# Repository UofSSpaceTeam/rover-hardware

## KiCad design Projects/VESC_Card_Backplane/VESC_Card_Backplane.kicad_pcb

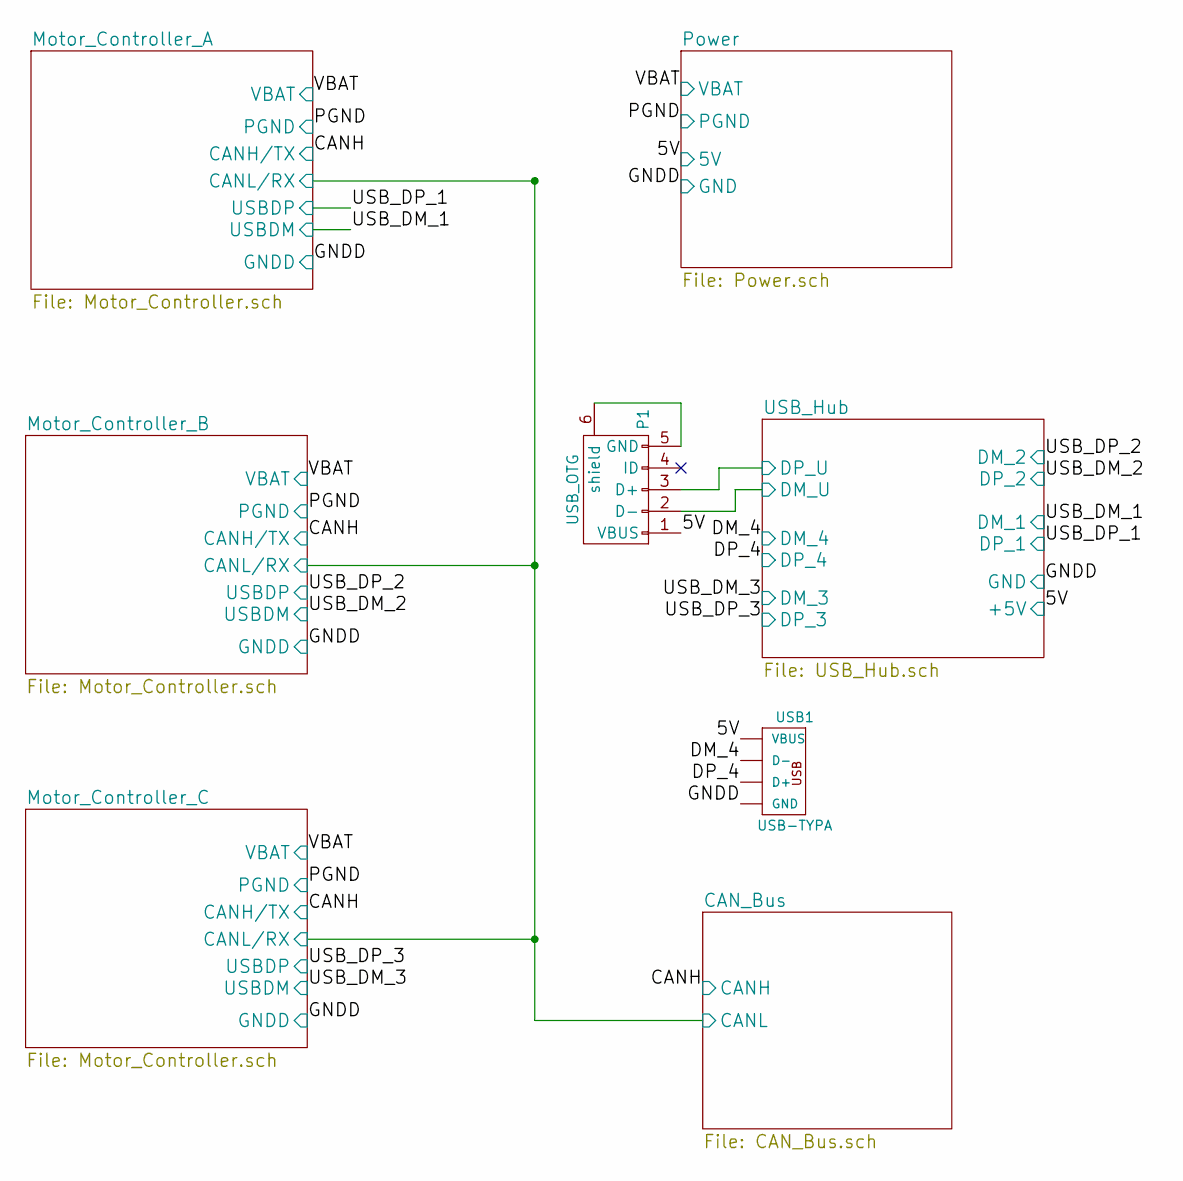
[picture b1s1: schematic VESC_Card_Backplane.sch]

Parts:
P1: USB_OTG; USB_Mini-B
USB1: USB-TYPA; USB_A_PTH_AMP787616-1

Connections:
/DM_4: USB1.D-; also elsewhere on the board
/DP_4: USB1.D+; also elsewhere on the board
/USB_Hub/DM_U: P1.2 (D-); also elsewhere on the board
/USB_Hub/DP_U: P1.3 (D+); also elsewhere on the board

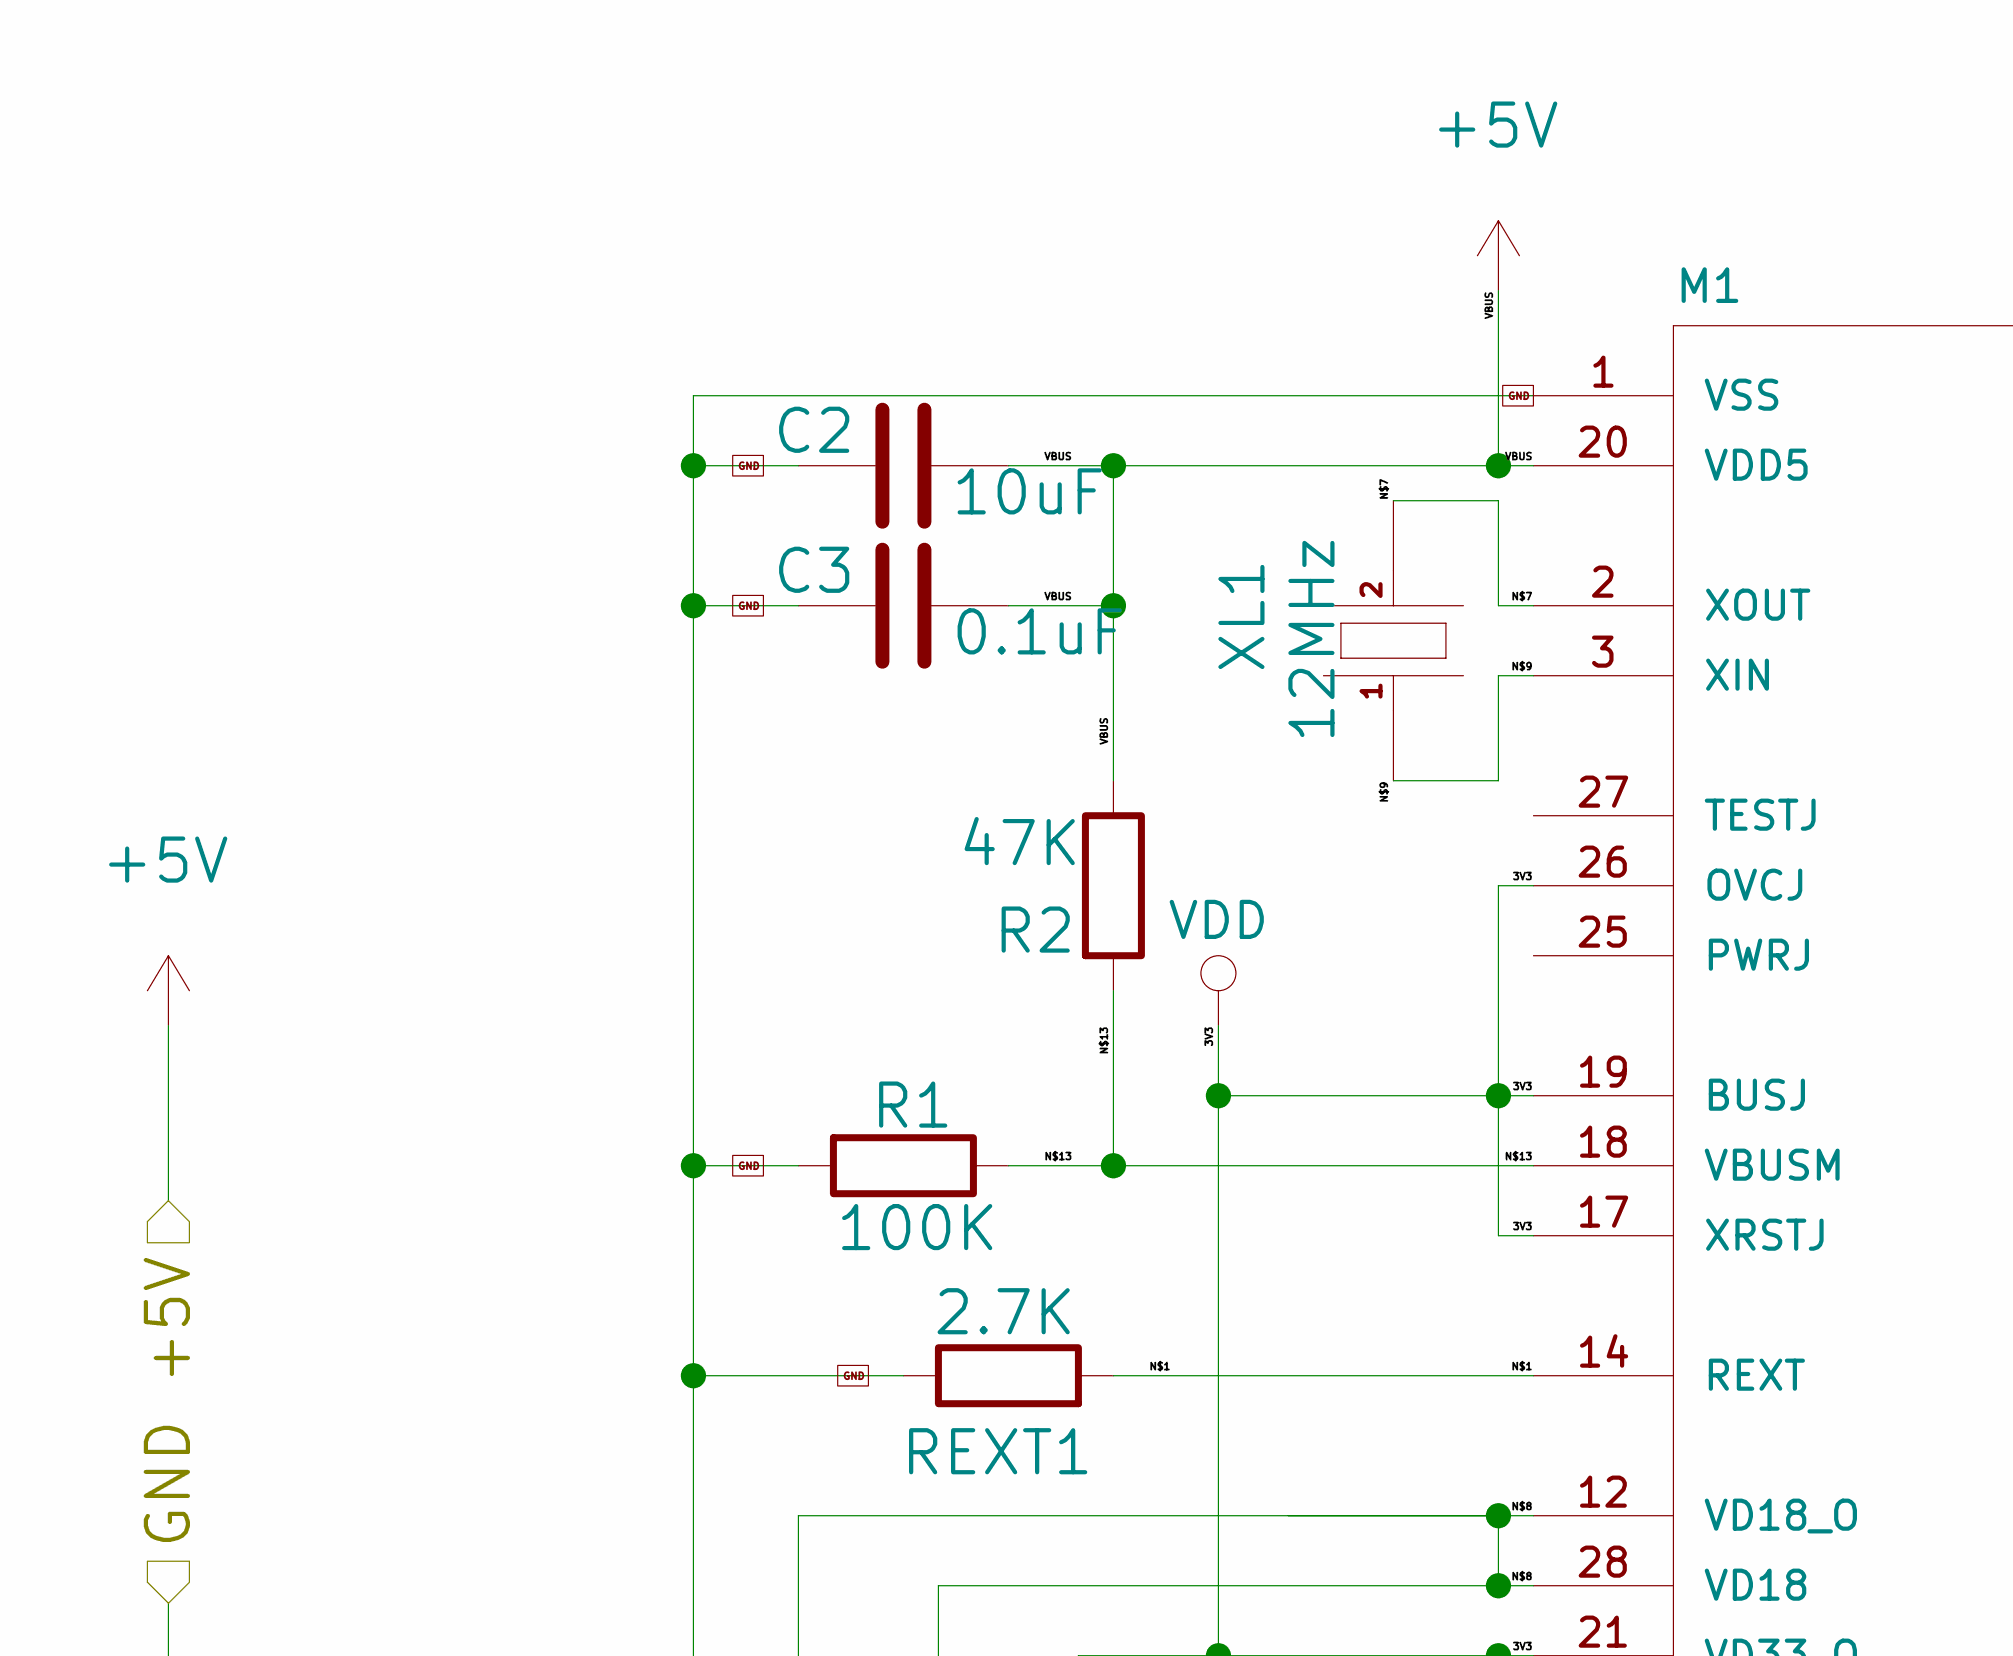
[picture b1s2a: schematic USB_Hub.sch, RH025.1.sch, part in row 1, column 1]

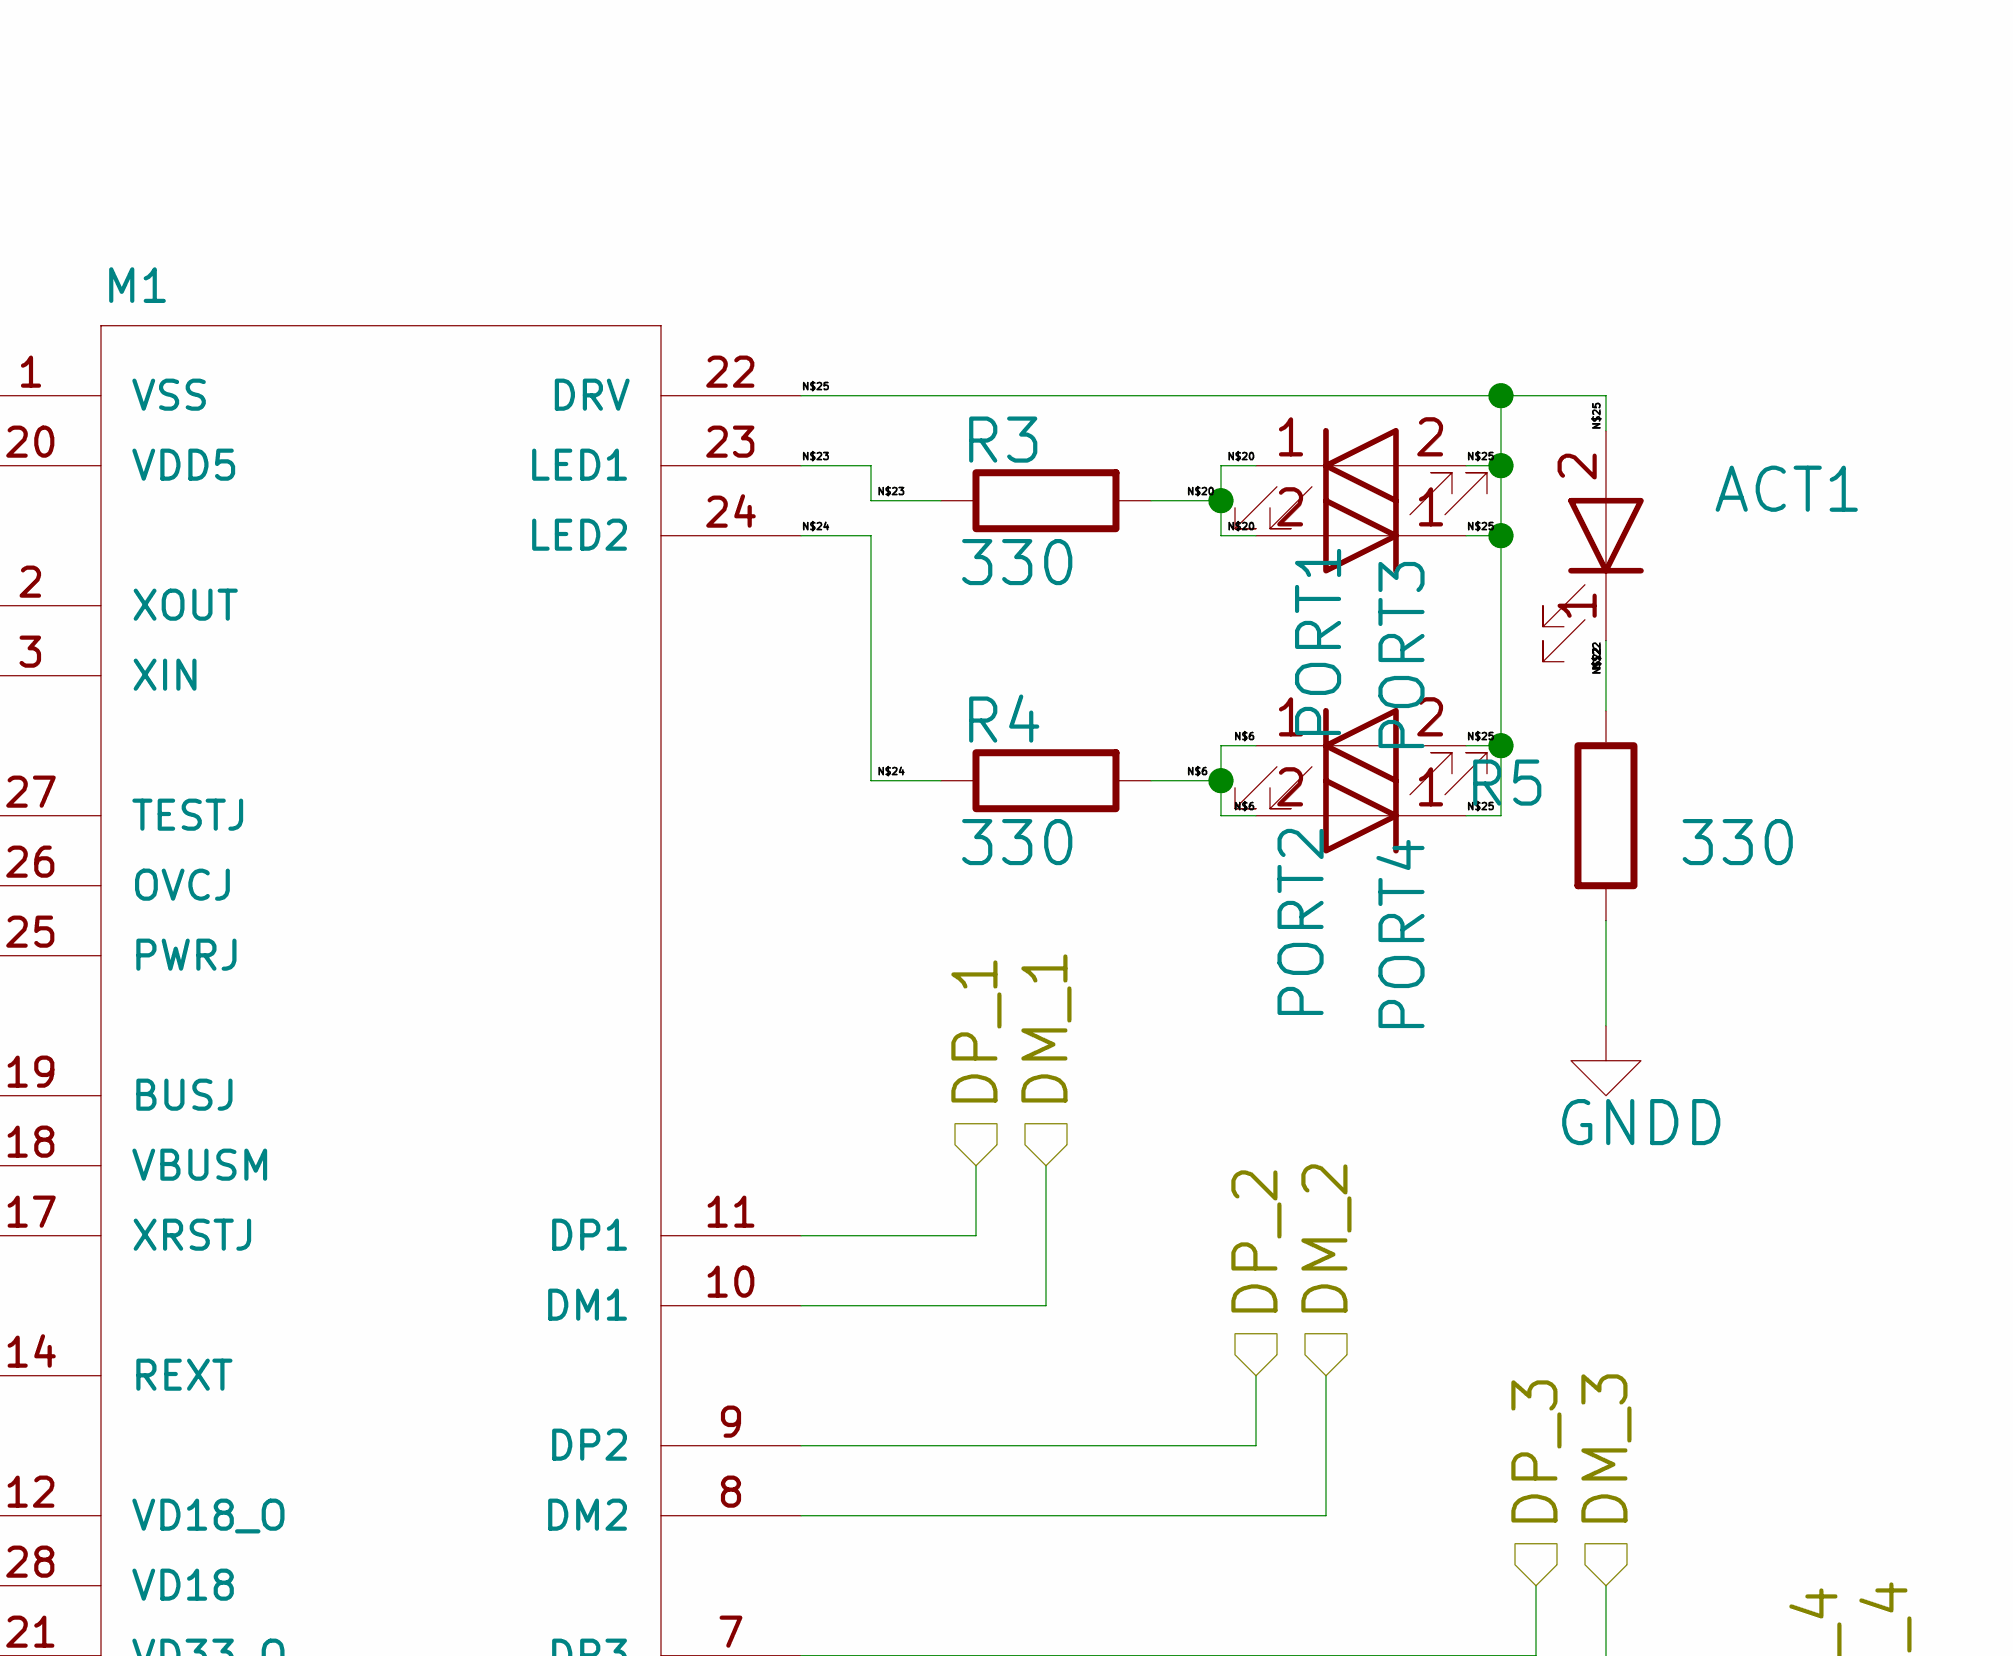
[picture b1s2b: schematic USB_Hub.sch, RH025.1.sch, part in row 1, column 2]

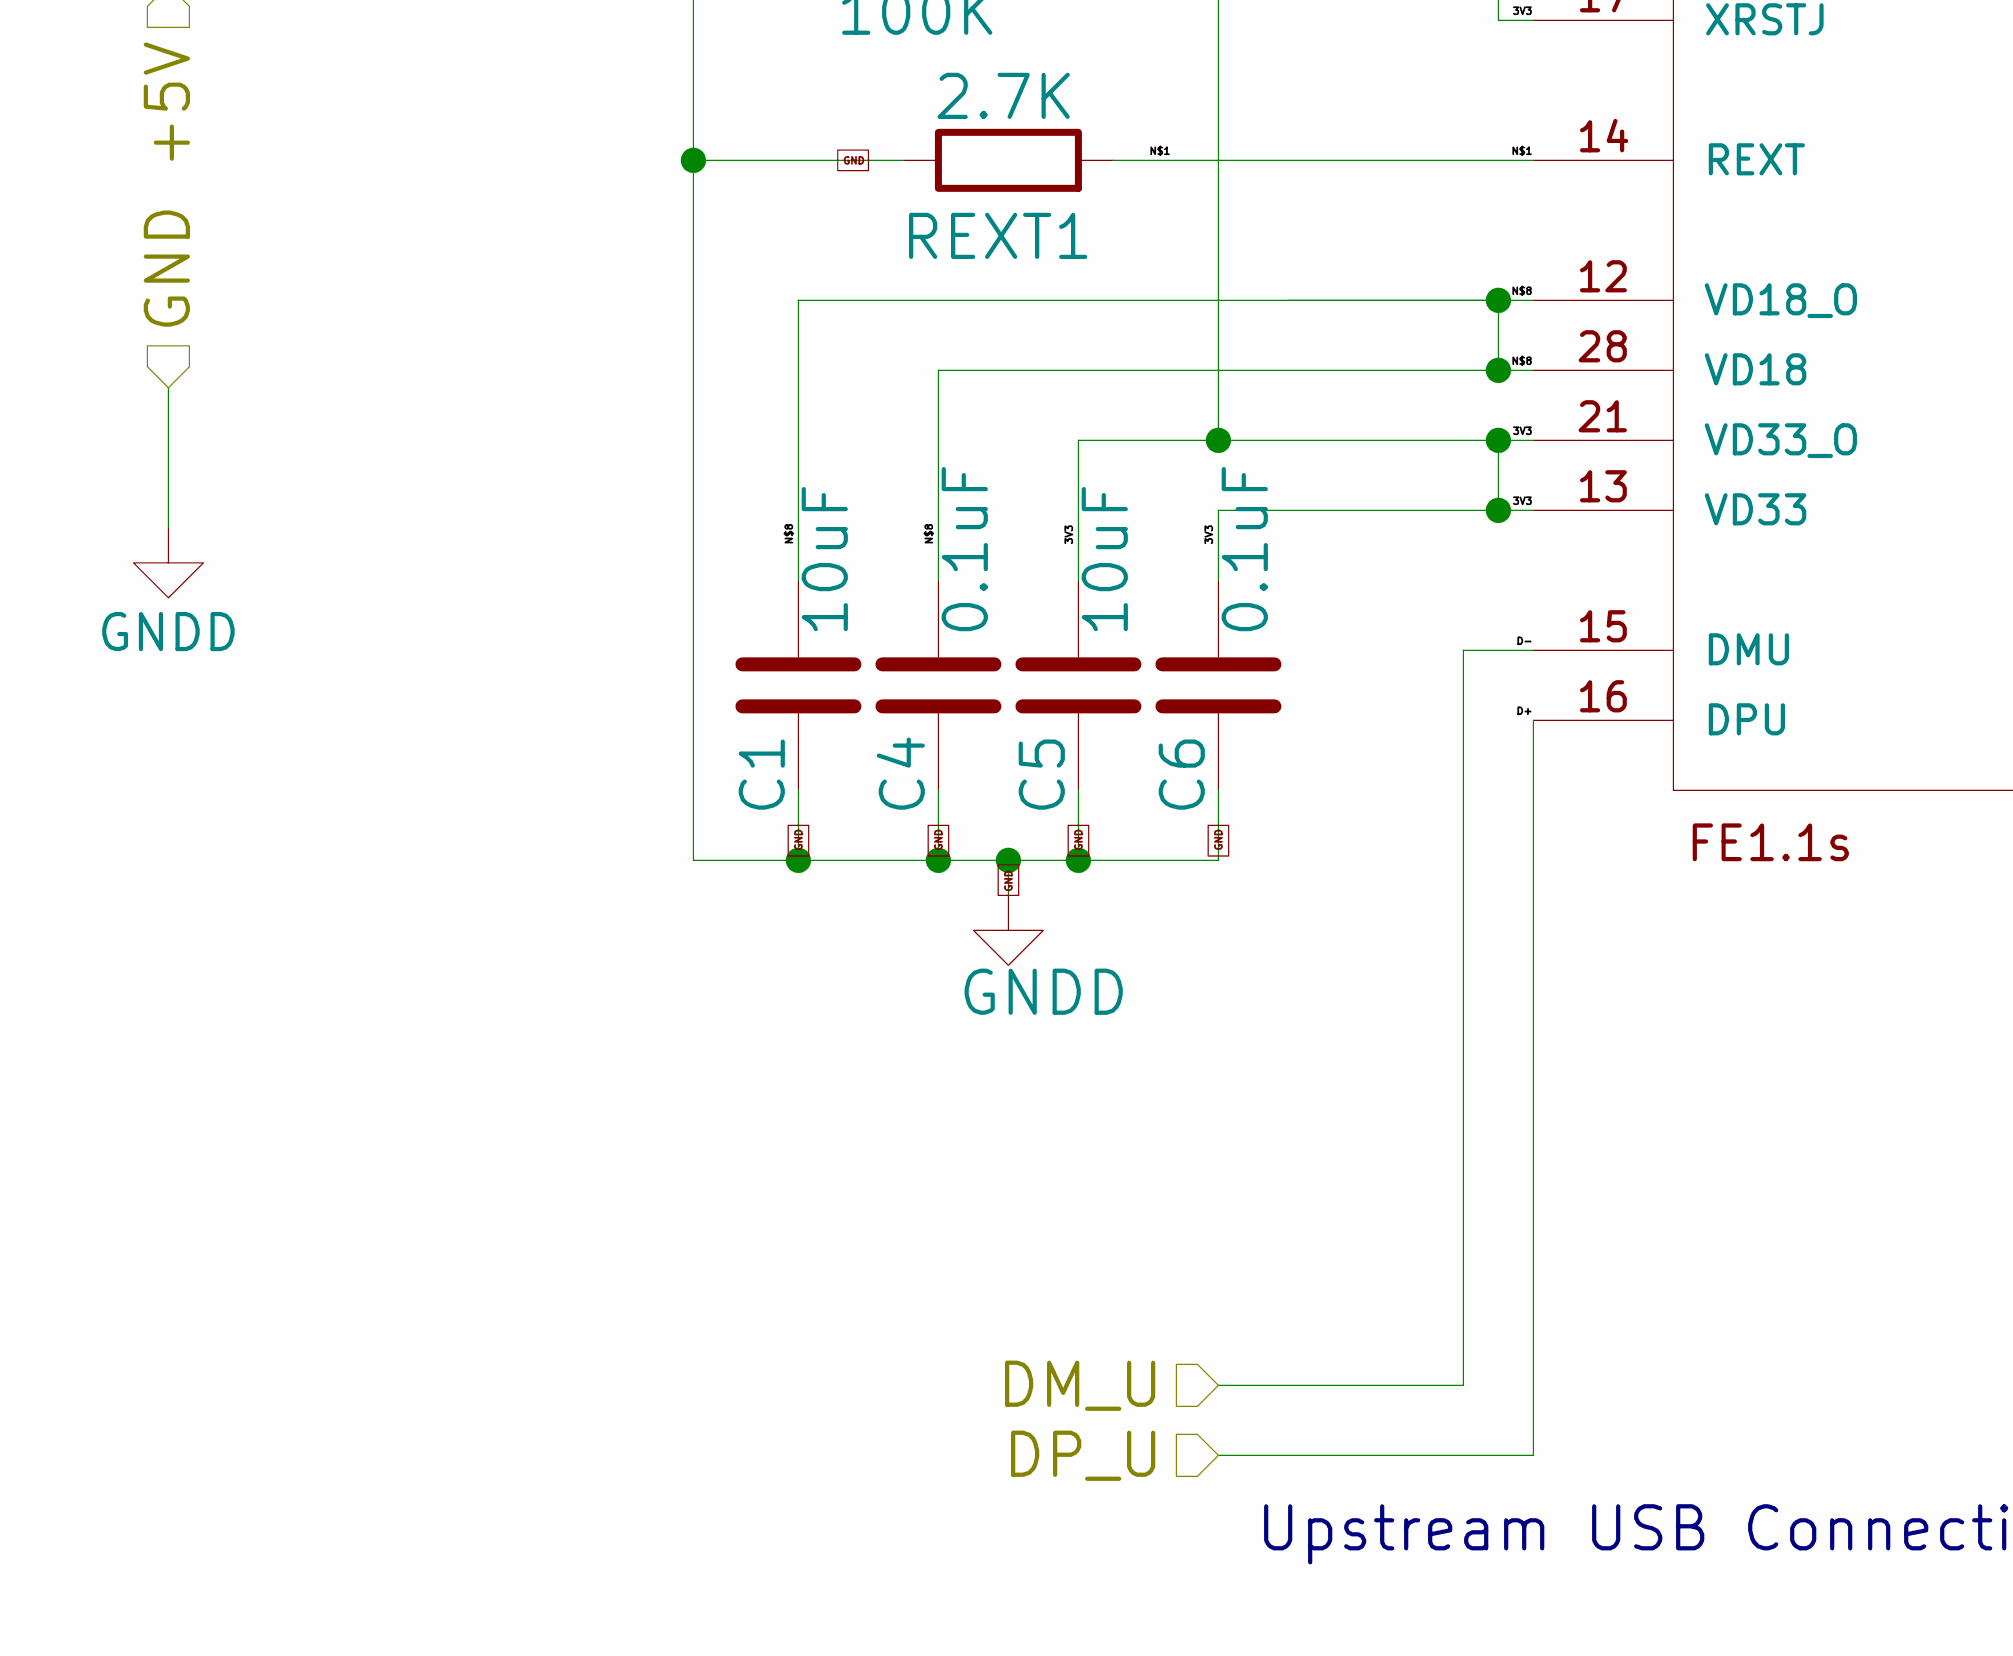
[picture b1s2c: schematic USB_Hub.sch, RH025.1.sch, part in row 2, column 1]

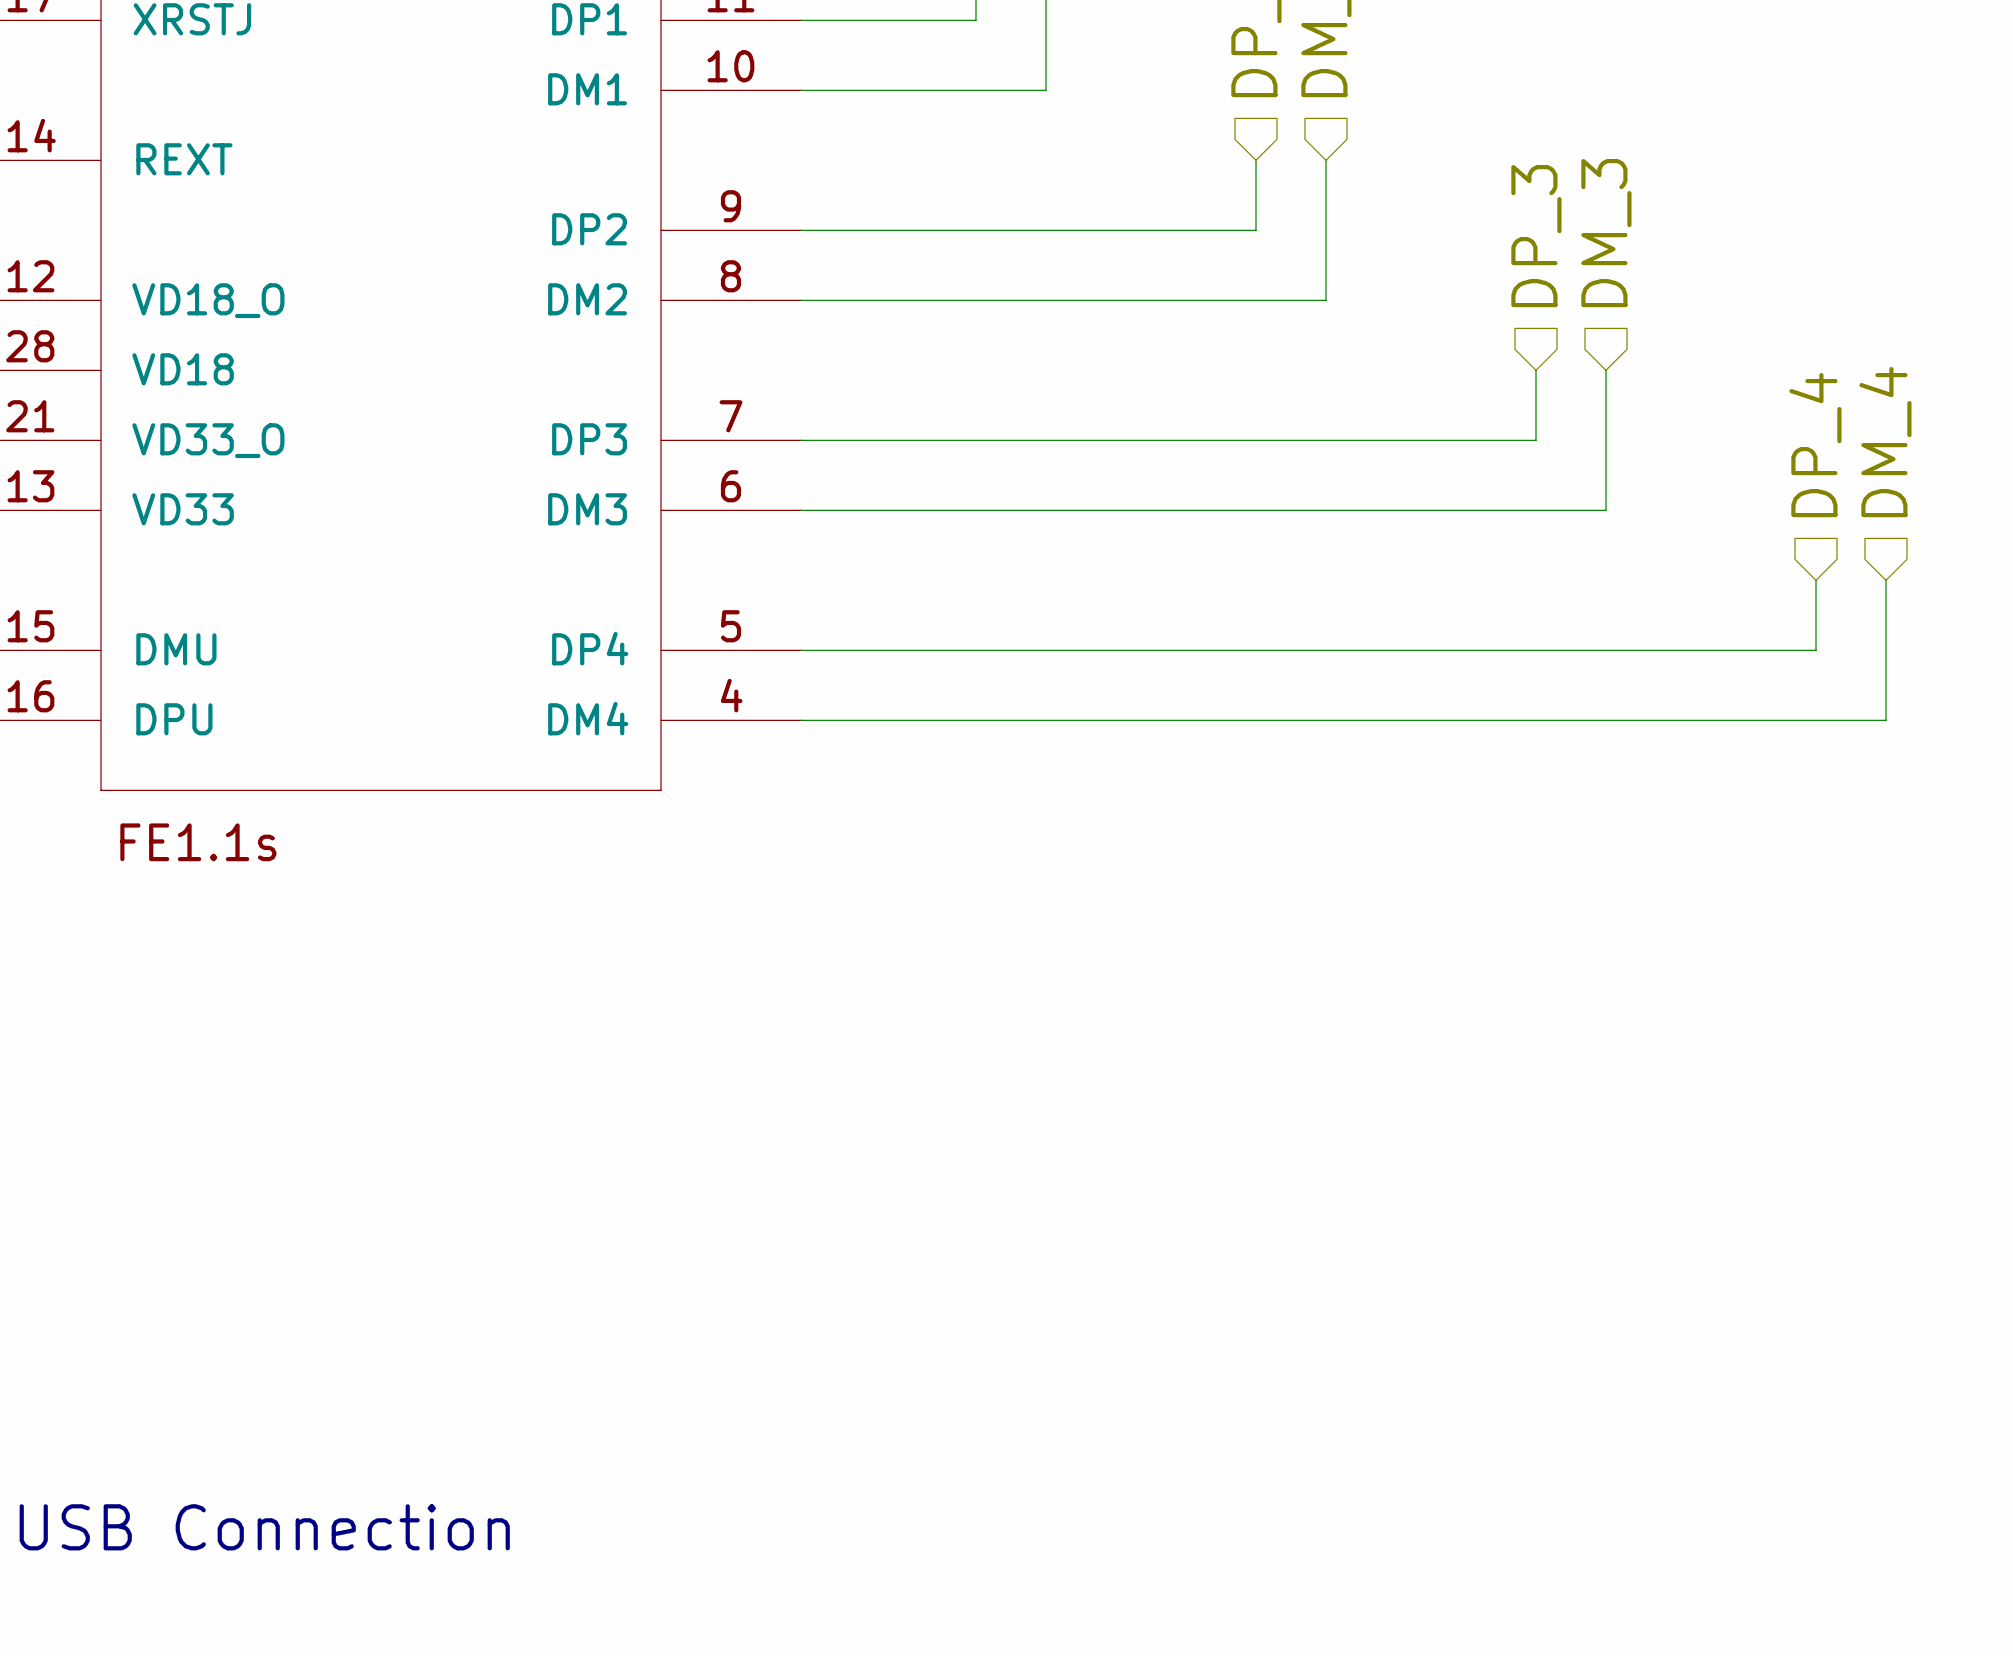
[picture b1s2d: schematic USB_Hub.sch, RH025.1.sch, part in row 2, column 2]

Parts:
ACT1: LED_0805
C1, C2, C5: 10uF; C_0805
C3, C4, C6: 0.1uF; C_0805
M1: FE1.1S; FE1.1S_SSOP-28
PORT1, PORT2, PORT3, PORT4: LED_0805
R1: 100K; R_0805
R2: 47K; R_0805
R3, R4, R5: 330; R_0805
REXT1: 2.7K; R_0805
XL1: 12MHz; HC49UP_SMT_Crystal

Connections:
/DM_4: M1.4 (DM4); also elsewhere on the board
/DP_4: M1.5 (DP4); also elsewhere on the board
/USB_DM_1: M1.10 (DM1); also elsewhere on the board
/USB_DM_2: M1.8 (DM2); also elsewhere on the board
/USB_DM_3: M1.6 (DM3); also elsewhere on the board
/USB_DP_1: M1.11 (DP1); also elsewhere on the board
/USB_DP_2: M1.9 (DP2); also elsewhere on the board
/USB_DP_3: M1.7 (DP3); also elsewhere on the board
/USB_Hub/DM_U: M1.15 (DMU); also elsewhere on the board
/USB_Hub/DP_U: M1.16 (DPU); also elsewhere on the board
/USB_Hub/N$1: M1.14 (REXT), REXT1.2
/USB_Hub/N$6: PORT2.1 (K), PORT4.2 (A), R4.2
/USB_Hub/N$7: M1.2 (XOUT), XL1.2
/USB_Hub/N$8: C1.1, C4.1, M1.12 (VD18_O), M1.28 (VD18)
/USB_Hub/N$9: M1.3 (XIN), XL1.1
/USB_Hub/N$13: M1.18 (VBUSM), R1.1, R2.2
/USB_Hub/N$20: PORT1.1 (K), PORT3.2 (A), R3.2
/USB_Hub/N$22: ACT1.1 (K), R5.1
/USB_Hub/N$23: M1.23 (LED1), R3.1
/USB_Hub/N$24: M1.24 (LED2), R4.1
/USB_Hub/N$25: ACT1.2 (A), M1.22 (DRV), PORT1.2 (A), PORT2.2 (A), PORT3.1 (K), PORT4.1 (K)
VDD: C5.1, C6.1, M1.13 (VD33), M1.17 (XRSTJ), M1.19 (BUSJ), M1.21 (VD33_O), M1.26 (OVCJ)

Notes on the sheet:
Upstream USB Connection

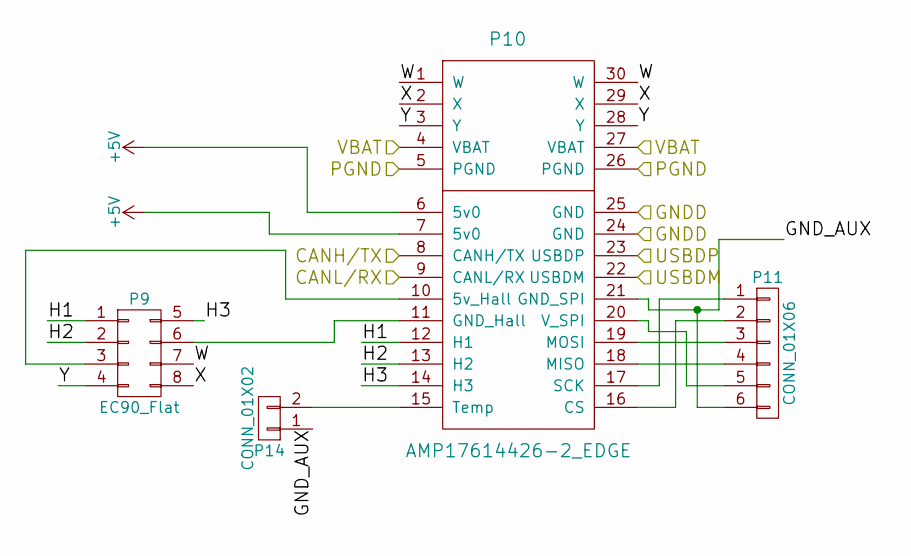
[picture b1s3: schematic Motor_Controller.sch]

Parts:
P2: EC90_Flat; Molex_MiniFit-JR-5569-08A2_2x04x4.20mm_Angled_Overhang
P3: AMP17614426-2_EDGE; TE2007088-1_Backplane
P4: CONN_01X06; Pin_Header_Angled_2x03_Pitch2.54mm
P12: CONN_01X02; Pin_Header_Straight_2x01_Pitch1.27mm

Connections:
/CANH: P3.8 (CANH/TX); also elsewhere on the board
/CAN_Bus/CANL: P3.9 (CANL/RX); also elsewhere on the board
/Motor_Controller_A/GND_AUX: P3.21 (GND_SPI), P4.6, P12.1
/Motor_Controller_A/H1: P2.1, P3.12 (H1)
/Motor_Controller_A/H2: P2.2, P3.13 (H2)
/Motor_Controller_A/H3: P2.5, P3.14 (H3)
/Motor_Controller_A/W: P2.7, P3.1 (W), P3.30 (W)
/Motor_Controller_A/X: P2.8, P3.2 (X), P3.29 (X)
/Motor_Controller_A/Y: P2.4, P3.3 (Y), P3.28 (Y)
/PGND: P3.5 (PGND), P3.24 (GND), P3.25 (GND), P3.26 (PGND); also elsewhere on the board
/USB_DM_1: P3.22 (USBDM); also elsewhere on the board
/USB_DP_1: P3.23 (USBDP); also elsewhere on the board
/VBAT: P3.4 (VBAT), P3.27 (VBAT); also elsewhere on the board
unnamed: P2.3, P3.10 (5v_Hall)
unnamed: P2.6, P3.11 (GND_Hall)
unnamed: P3.16 (CS), P4.2
unnamed: P3.17 (SCK), P4.1
unnamed: P3.18 (MISO), P4.4
unnamed: P3.19 (MOSI), P4.3
unnamed: P3.20 (V_SPI), P4.5
unnamed: P3.15 (Temp), P12.2

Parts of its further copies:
P6, P9: EC90_Flat; Molex_MiniFit-JR-5569-08A2_2x04x4.20mm_Angled_Overhang
P7, P10: AMP17614426-2_EDGE; TE2007088-1_Backplane
P8, P11: CONN_01X06; Pin_Header_Angled_2x03_Pitch2.54mm
P13, P14: CONN_01X02; Pin_Header_Straight_2x01_Pitch1.27mm

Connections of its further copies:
/CANH: P7.8 (CANH/TX), P10.8 (CANH/TX); also elsewhere on the board
/CAN_Bus/CANL: P7.9 (CANL/RX), P10.9 (CANL/RX); also elsewhere on the board
/Motor_Controller_B/GND_AUX: P7.21 (GND_SPI), P8.6, P13.1
/Motor_Controller_B/H1: P6.1, P7.12 (H1)
/Motor_Controller_B/H2: P6.2, P7.13 (H2)
/Motor_Controller_B/H3: P6.5, P7.14 (H3)
/Motor_Controller_B/W: P6.7, P7.1 (W), P7.30 (W)
/Motor_Controller_B/X: P6.8, P7.2 (X), P7.29 (X)
/Motor_Controller_B/Y: P6.4, P7.3 (Y), P7.28 (Y)
/Motor_Controller_C/GND_AUX: P10.21 (GND_SPI), P11.6, P14.1
/Motor_Controller_C/H1: P9.1, P10.12 (H1)
/Motor_Controller_C/H2: P9.2, P10.13 (H2)
/Motor_Controller_C/H3: P9.5, P10.14 (H3)
/Motor_Controller_C/W: P9.7, P10.1 (W), P10.30 (W)
/Motor_Controller_C/X: P9.8, P10.2 (X), P10.29 (X)
/Motor_Controller_C/Y: P9.4, P10.3 (Y), P10.28 (Y)
/PGND: P7.5 (PGND), P7.24 (GND), P7.25 (GND), P7.26 (PGND), P10.5 (PGND), P10.26 (PGND); also elsewhere on the board
/USB_DM_2: P7.22 (USBDM); also elsewhere on the board
/USB_DM_3: P10.22 (USBDM); also elsewhere on the board
/USB_DP_2: P7.23 (USBDP); also elsewhere on the board
/USB_DP_3: P10.23 (USBDP); also elsewhere on the board
/VBAT: P7.4 (VBAT), P7.27 (VBAT), P10.4 (VBAT), P10.27 (VBAT); also elsewhere on the board
unnamed: P6.3, P7.10 (5v_Hall)
unnamed: P6.6, P7.11 (GND_Hall)
unnamed: P7.16 (CS), P8.2
unnamed: P7.17 (SCK), P8.1
unnamed: P7.18 (MISO), P8.4
unnamed: P7.19 (MOSI), P8.3
unnamed: P7.20 (V_SPI), P8.5
unnamed: P9.3, P10.10 (5v_Hall)
unnamed: P9.6, P10.11 (GND_Hall)
unnamed: P10.15 (Temp), P14.2
unnamed: P10.16 (CS), P11.2
unnamed: P10.17 (SCK), P11.1
unnamed: P10.18 (MISO), P11.4
unnamed: P10.19 (MOSI), P11.3
unnamed: P10.20 (V_SPI), P11.5
unnamed: P7.15 (Temp), P13.2

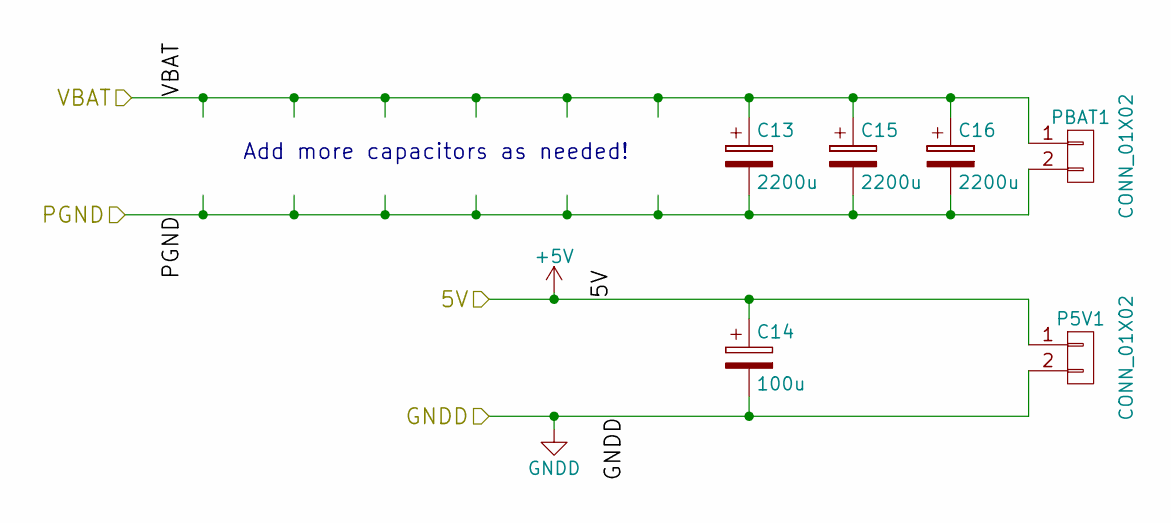
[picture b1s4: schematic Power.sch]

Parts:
C13, C15, C16: 2200u; CP_Radial_D16.0mm_P7.50mm
C14: 100u; CP_Radial_D8.0mm_P3.80mm
P5V1: CONN_01X02; Molex_39531_1002
PBAT1: CONN_01X02; Phoenix_Contact_PLA5

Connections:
/PGND: C13.2, C15.2, C16.2, PBAT1.2; also elsewhere on the board
/VBAT: C13.1, C15.1, C16.1, PBAT1.1; also elsewhere on the board

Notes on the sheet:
Add more capacitors as needed!

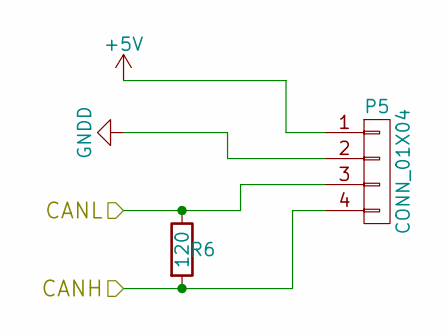
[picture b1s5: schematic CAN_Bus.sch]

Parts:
P5: CONN_01X04; Molex_39502_1004R
R6: 120; R_0805

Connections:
/CANH: P5.4, R6.2; also elsewhere on the board
/CAN_Bus/CANL: P5.3, R6.1; also elsewhere on the board

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
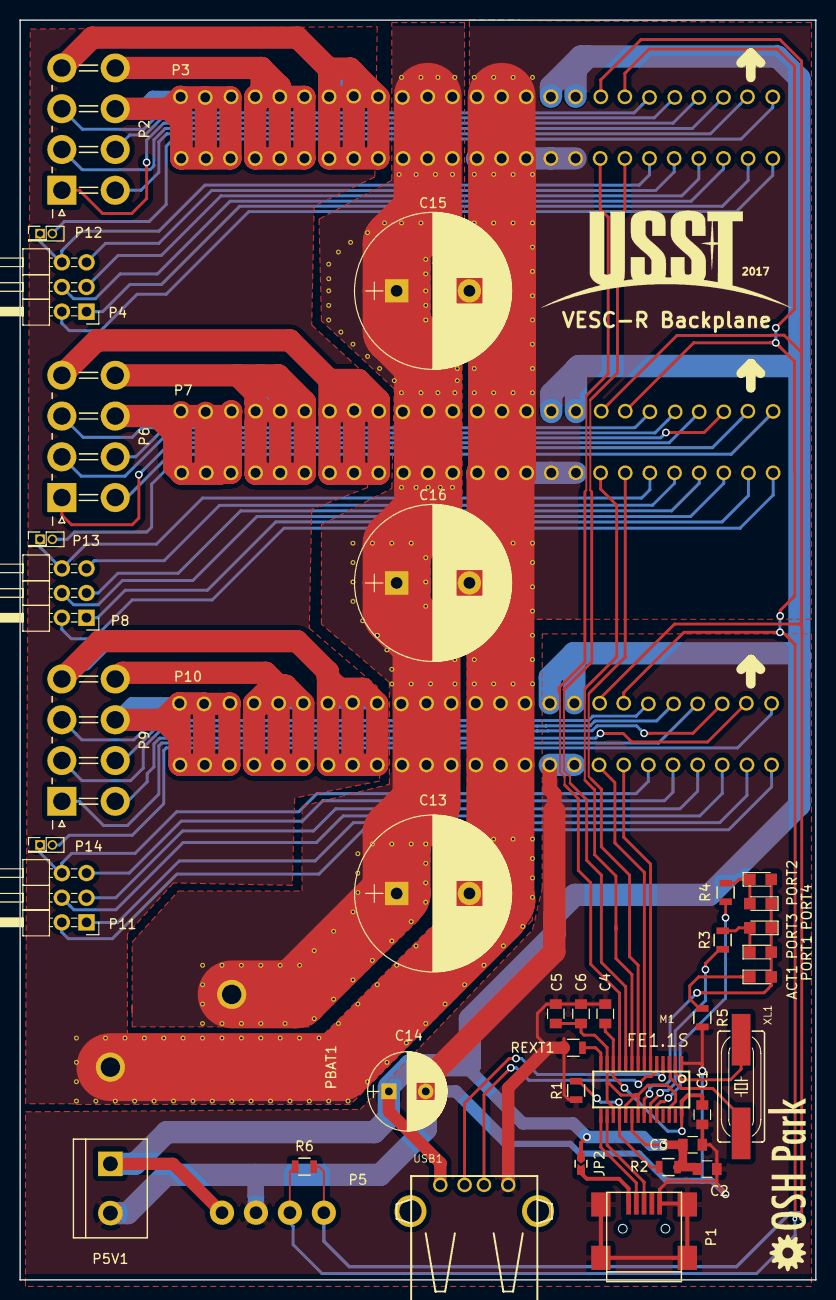
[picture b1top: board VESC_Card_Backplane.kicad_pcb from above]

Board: 2 copper layers, 82.0 x 129.8 mm, 42 parts (0 on the bottom side), 74 nets.

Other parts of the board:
JP2: J; J_0603

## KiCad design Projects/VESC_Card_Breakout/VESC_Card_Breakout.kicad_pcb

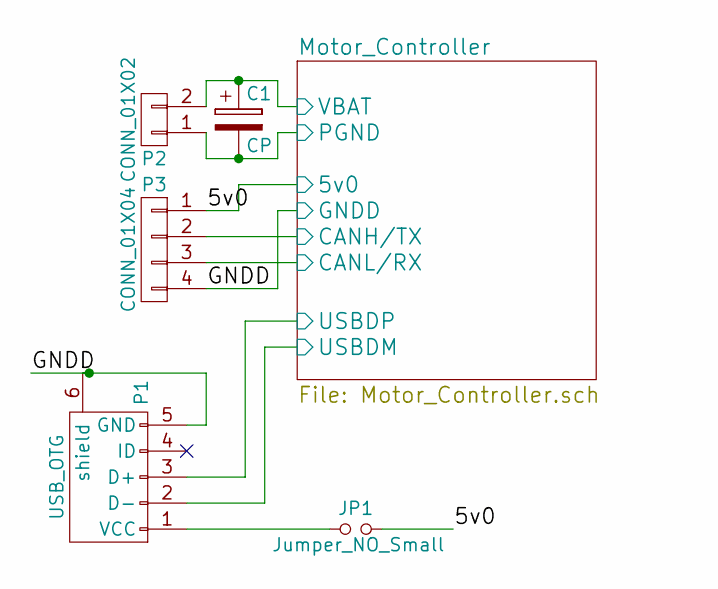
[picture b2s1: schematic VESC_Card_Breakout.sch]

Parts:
C1: CP; CP_Elec_10x10
JP1: Jumper_NO_Small; J_0603
P1: USB_OTG; USB_Mini-B
P2: CONN_01X02; Molex_MiniFit-JR-5569-02A2_2x01x4.20mm_Angled
P3: CONN_01X04; Molex_39502_1004R

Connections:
/5v0: JP1.2, P3.1; also elsewhere on the board
/Motor_Controller/CANL/RX: P3.3; also elsewhere on the board
/Motor_Controller/PGND: C1.2, P2.1; also elsewhere on the board
/Motor_Controller/USBDM: P1.2 (D-); also elsewhere on the board
/Motor_Controller/USBDP: P1.3 (D+); also elsewhere on the board
/Motor_Controller/VBAT: C1.1, P2.2; also elsewhere on the board
unnamed: JP1.1, P1.1 (VCC)

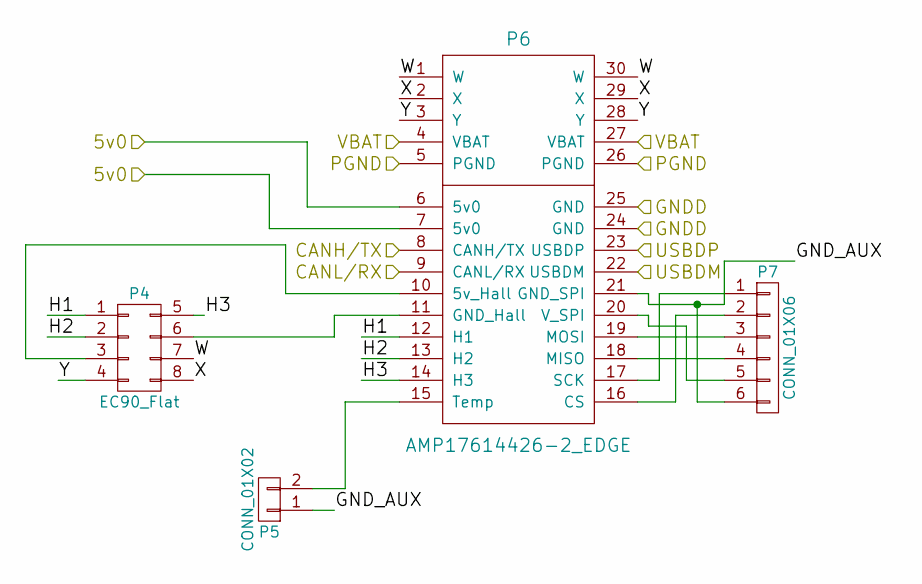
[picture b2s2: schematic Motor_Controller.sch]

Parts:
P4: EC90_Flat; Molex_MiniFit-JR-5569-08A2_2x04x4.20mm_Angled_Overhang
P5: CONN_01X02; Pin_Header_Straight_2x01_Pitch1.27mm
P6: AMP17614426-2_EDGE; TE2007088-1_Backplane
P7: CONN_01X06; Pin_Header_Angled_2x03_Pitch2.54mm

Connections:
/5v0: P6.6 (5v0), P6.7 (5v0); also elsewhere on the board
/Motor_Controller/CANL/RX: P6.9 (CANL/RX); also elsewhere on the board
/Motor_Controller/GND_AUX: P5.1, P6.21 (GND_SPI), P7.6
/Motor_Controller/H1: P4.1, P6.12 (H1)
/Motor_Controller/H2: P4.2, P6.13 (H2)
/Motor_Controller/H3: P4.5, P6.14 (H3)
/Motor_Controller/PGND: P6.5 (PGND), P6.26 (PGND); also elsewhere on the board
/Motor_Controller/USBDM: P6.22 (USBDM); also elsewhere on the board
/Motor_Controller/USBDP: P6.23 (USBDP); also elsewhere on the board
/Motor_Controller/VBAT: P6.4 (VBAT), P6.27 (VBAT); also elsewhere on the board
/Motor_Controller/W: P4.7, P6.1 (W), P6.30 (W)
/Motor_Controller/X: P4.8, P6.2 (X), P6.29 (X)
/Motor_Controller/Y: P4.4, P6.3 (Y), P6.28 (Y)
unnamed: P4.3, P6.10 (5v_Hall)
unnamed: P4.6, P6.11 (GND_Hall)
unnamed: P5.2, P6.15 (Temp)
unnamed: P6.16 (CS), P7.2
unnamed: P6.17 (SCK), P7.1
unnamed: P6.18 (MISO), P7.4
unnamed: P6.19 (MOSI), P7.3
unnamed: P6.20 (V_SPI), P7.5

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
